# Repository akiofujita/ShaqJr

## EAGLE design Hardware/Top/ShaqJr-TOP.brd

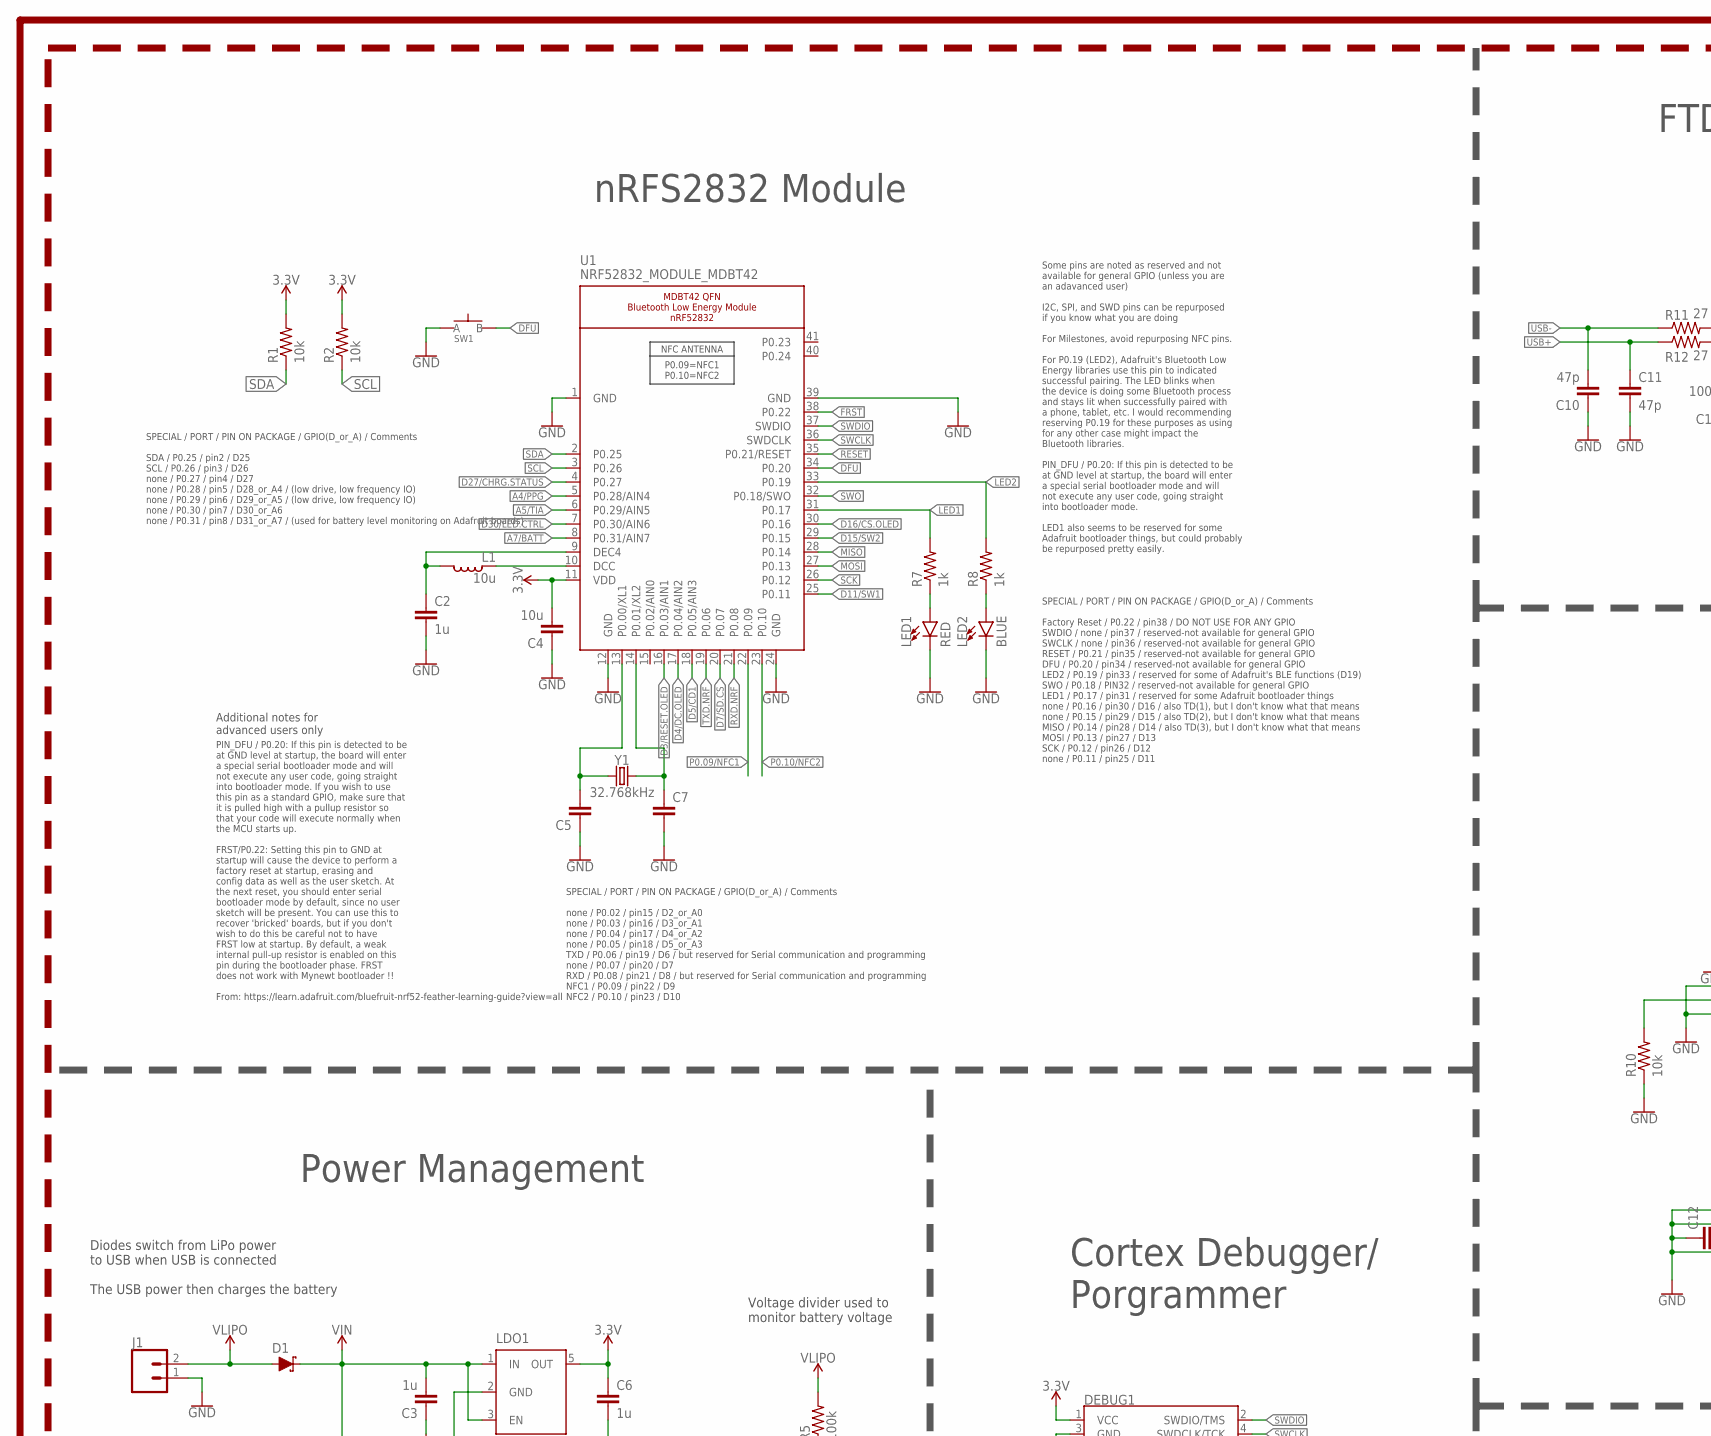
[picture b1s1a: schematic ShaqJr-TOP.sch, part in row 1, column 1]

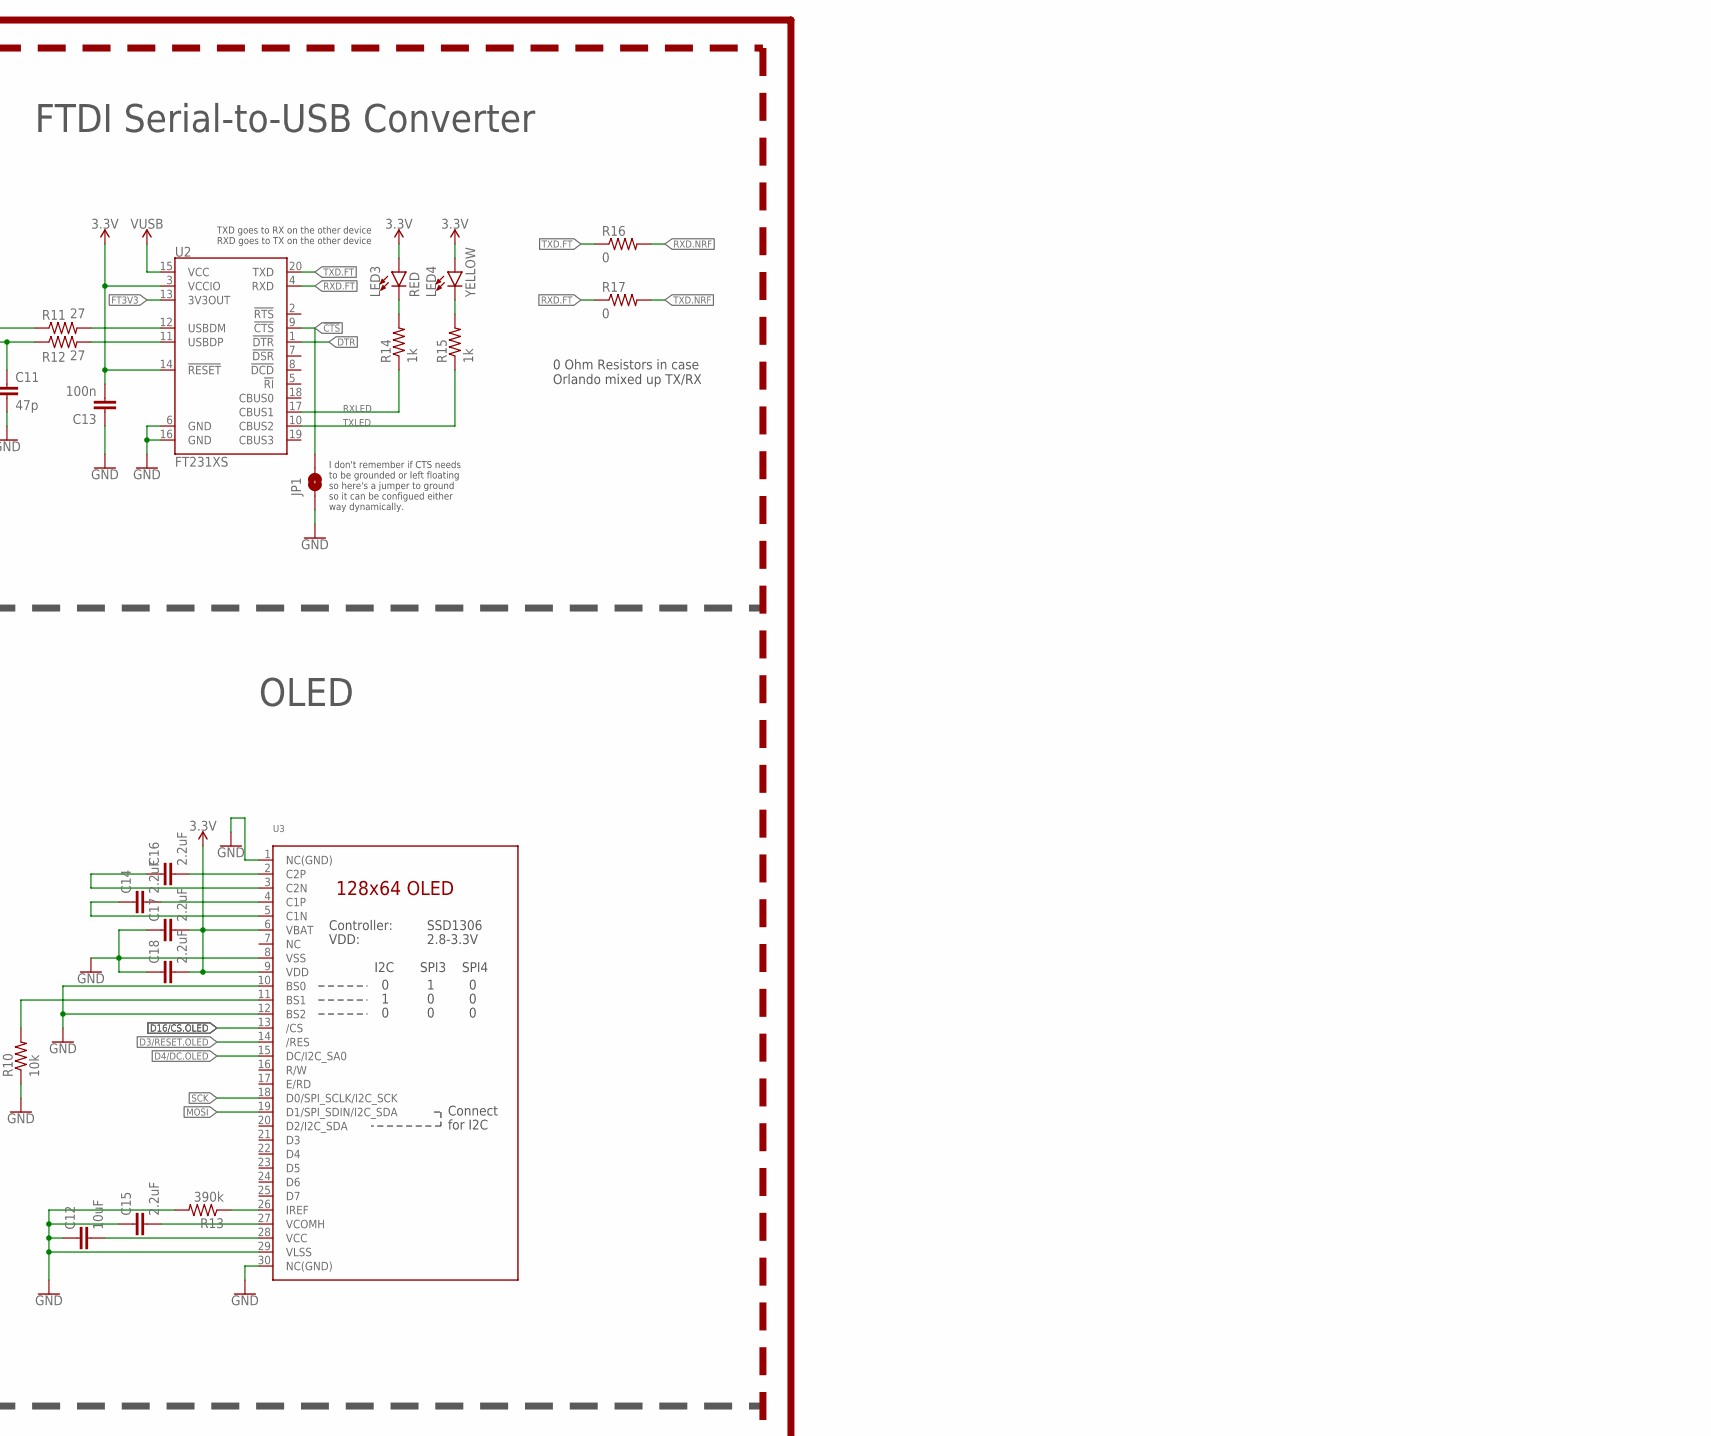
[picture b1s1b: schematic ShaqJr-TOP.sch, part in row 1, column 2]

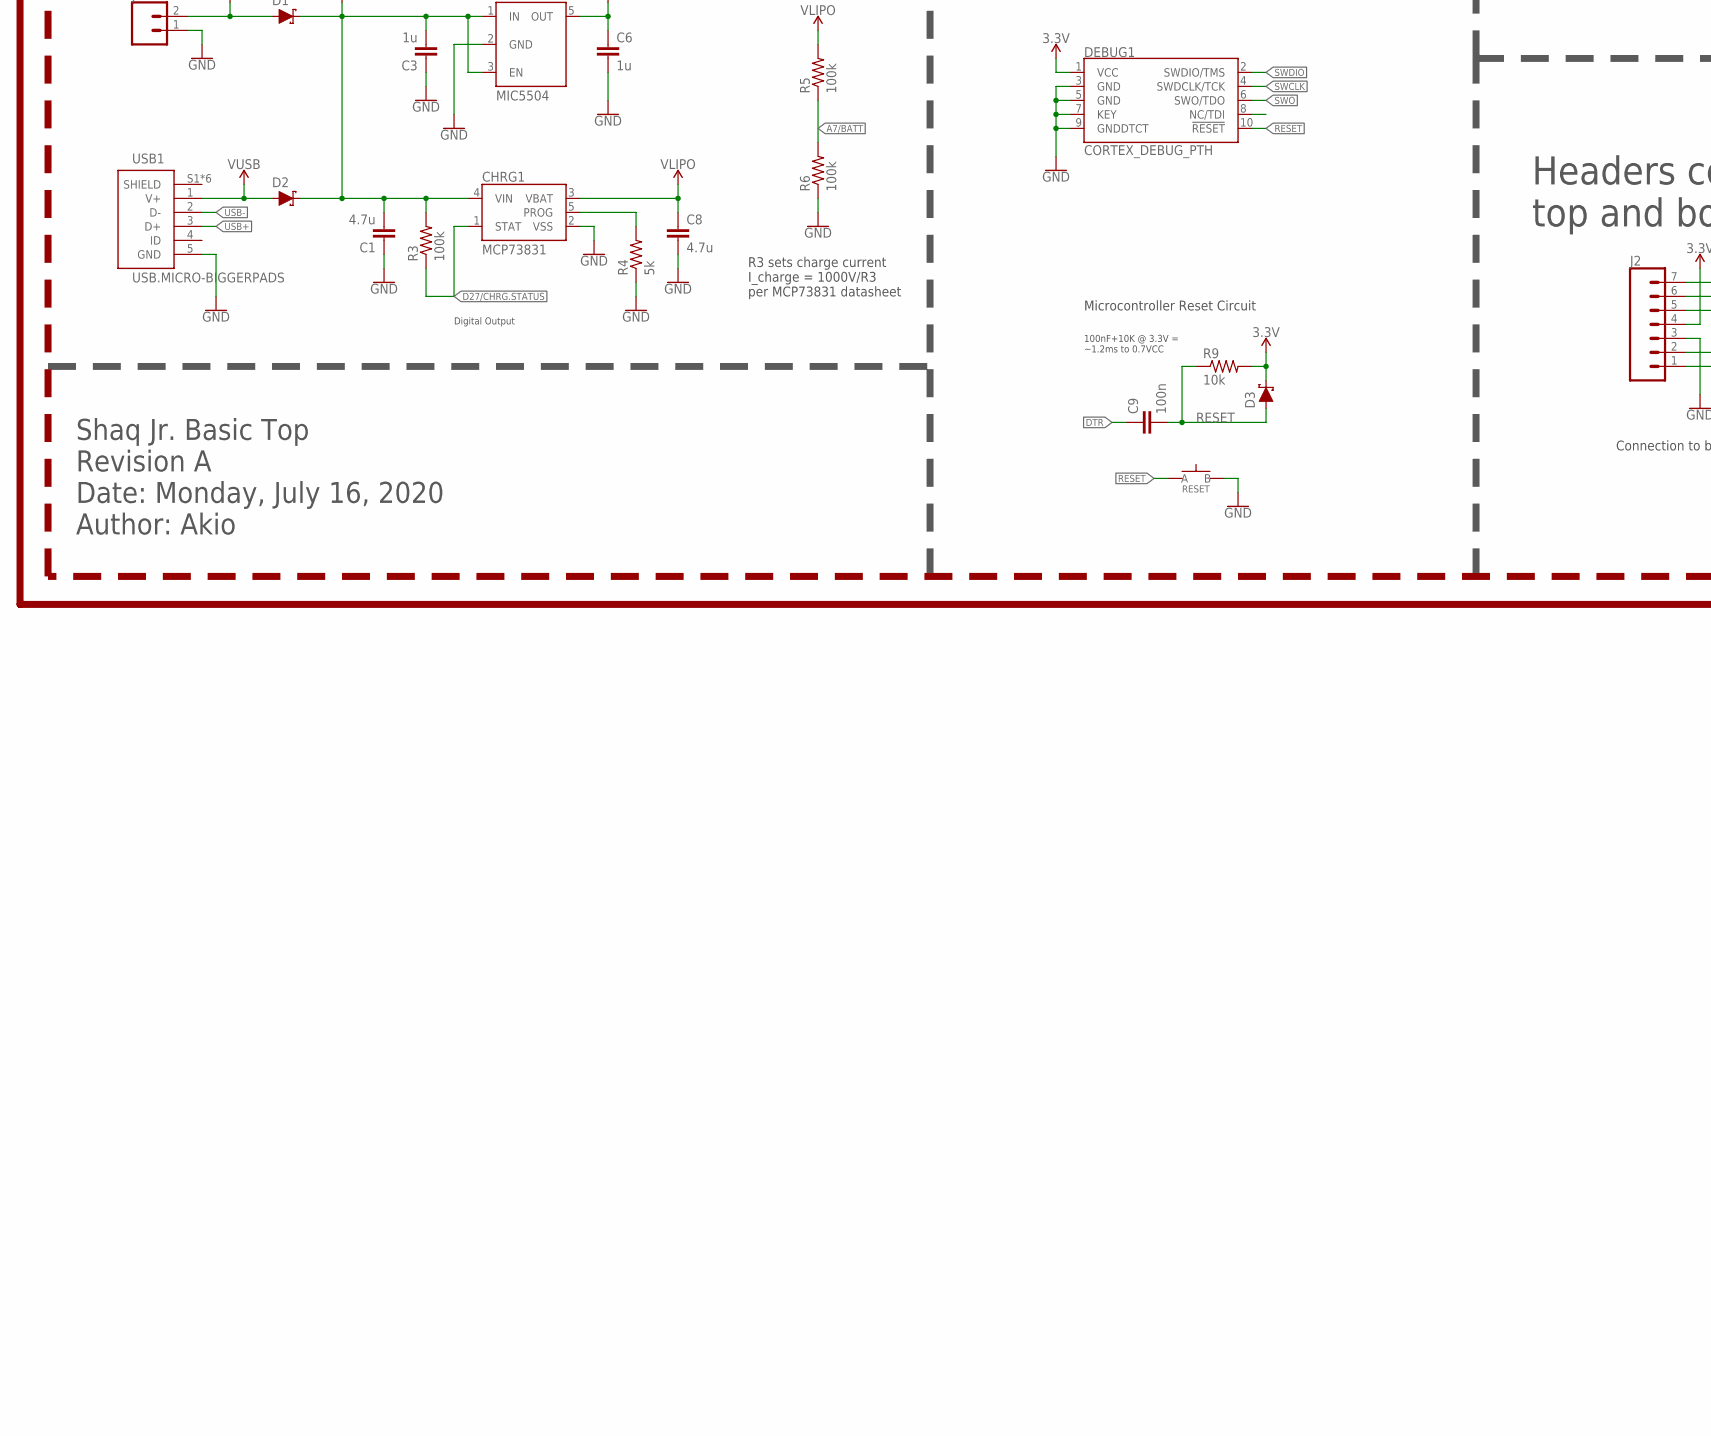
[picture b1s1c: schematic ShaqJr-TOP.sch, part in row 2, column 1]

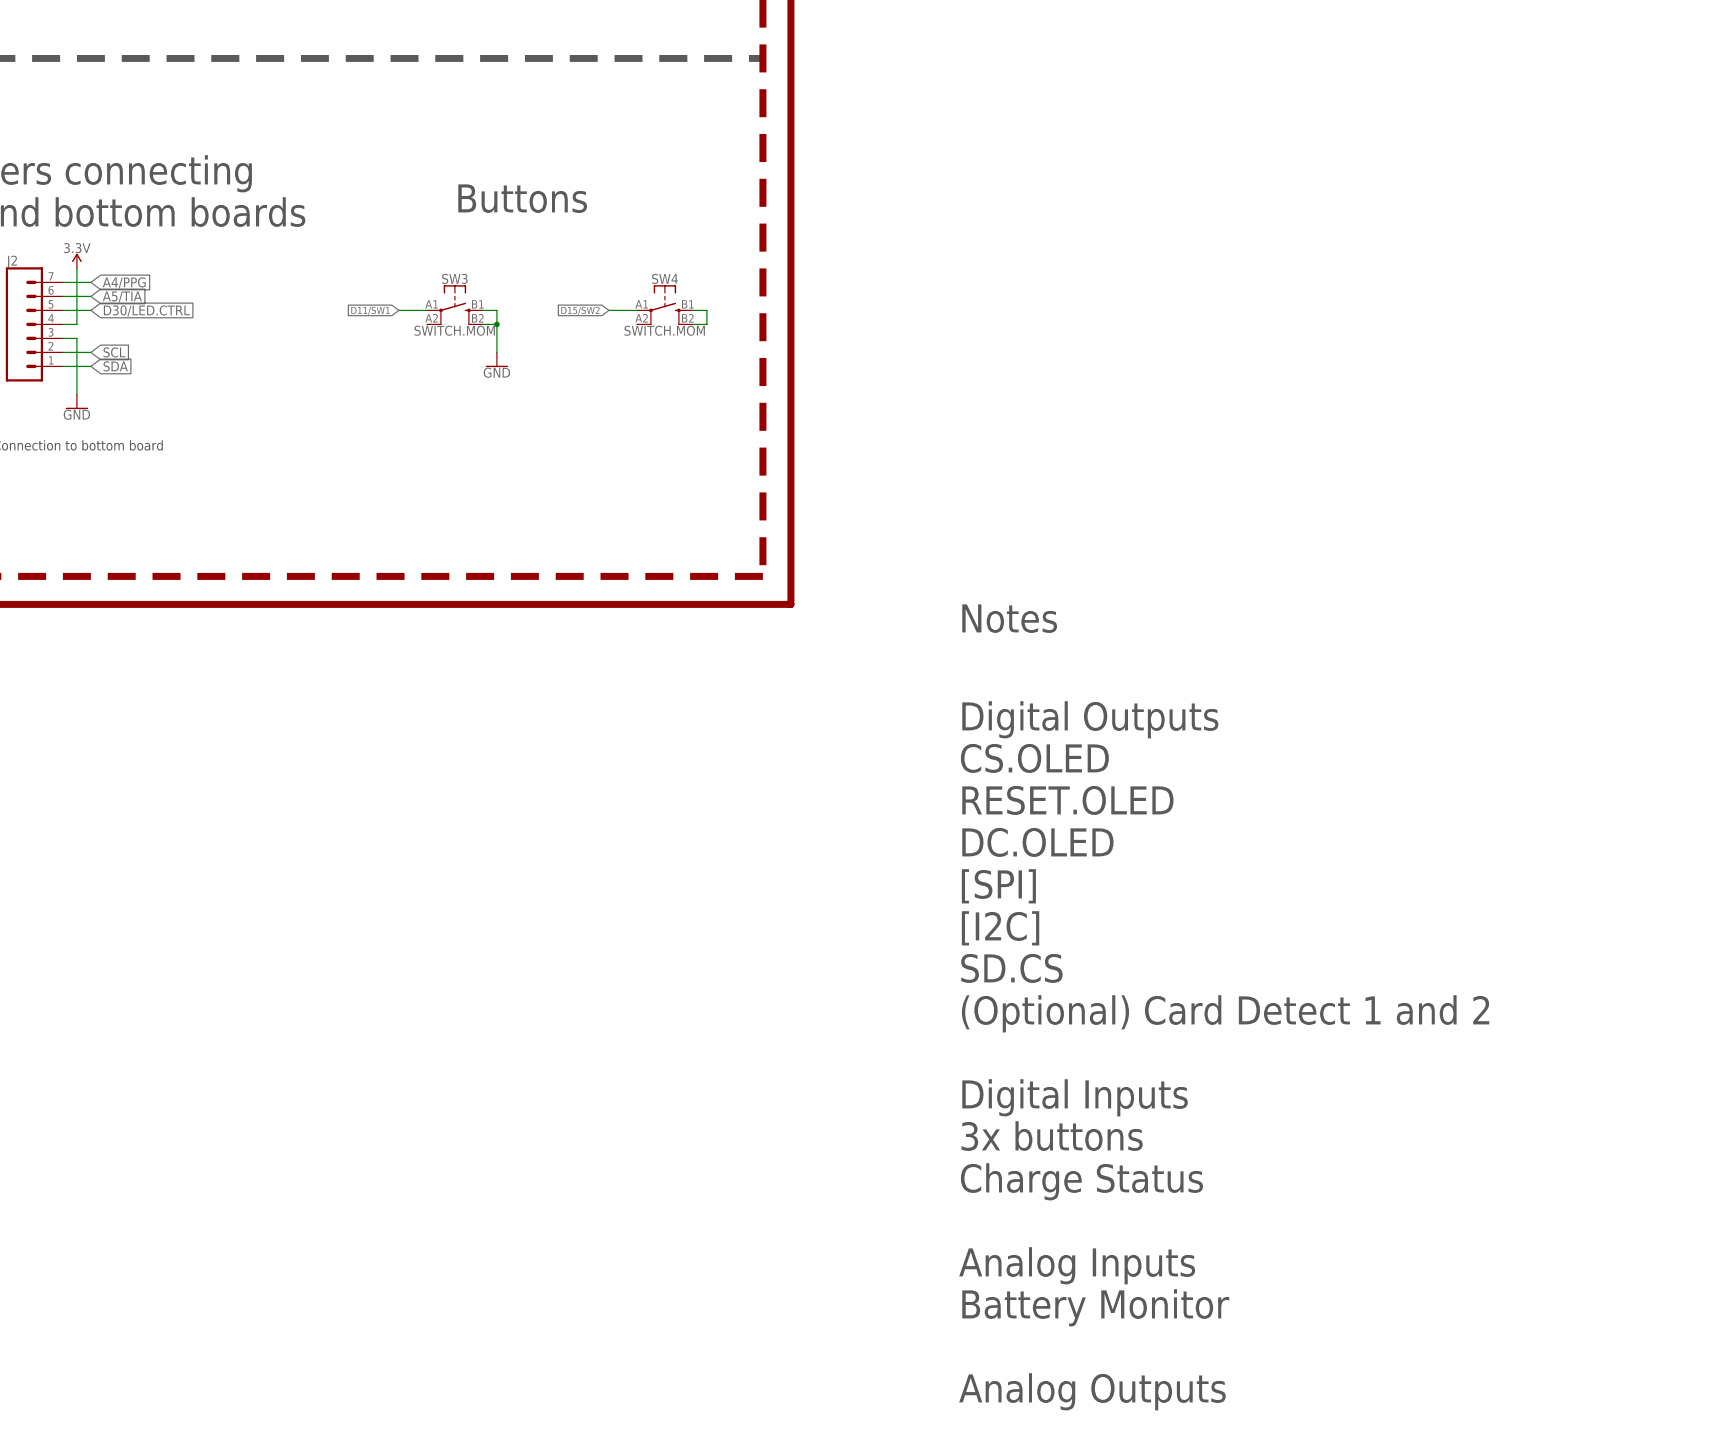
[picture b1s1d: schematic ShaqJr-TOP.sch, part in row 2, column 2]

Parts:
C1, C8: 4.7u; C0603
C2, C3, C6: 1u; C0603
C4: 10u; C0805
C5, C7: CAPACITOR0603; C0603
C9, C13: 100n; C0603
C10, C11: 47p; C0603
C12: 10uF; C0603
C14, C16, C17, C18: 2.2uF; C0402
C15: 2.2uF; C0603
CHRG1: MCP73831; SOT23-5
D1, D2, D3: SCHOTTKY-USC; USC
DEBUG1: CORTEX_DEBUG_PTH; 2X5-PTH-1.27MM
J1: CONN_02; 1X02
J2: CONN_07-1.27MM; 1X07_1.27MM
JP1: JUMPER-SMT_2_NO_SILK; SMT-JUMPER_2_NO_SILK
L1: 10u; L0603
LDO1: MIC5504; SOT23-5
LED1, LED3: RED; LED-0603
LED2: BLUE; LED-0603
LED4: YELLOW; LED-0603
R1, R2, R9, R10: 10k; R0603
R3, R5, R6: 100k; R0603
R4: 5k; R0603
R7, R8, R14, R15: 1k; R0603
R11, R12: 27; R0603
R13: 390k; R0603
R16, R17: 0; R0603
RESET: SPST-PTS830GG140-COPY.1-3; BUTTON-GULLWING
SW1: SPST-PTS830GG140-COPY.1-3; BUTTON-GULLWING
SW3, SW4: SWITCH.MOM; TACTILE_SWITCH_SMD_6.2MM_TALL
U1: NRF52832_MODULE_MDBT42; BLE_MODULE_RAYTAC_MDBT42
U2: FT231XS; SSOP20_L
U3: DISP_OLED_UG-2864HSWEG01-NO-WRAPAROUND; UG-2864HSWEG01_0.96IN_NO-WRAPAROUND
USB1: USB.MICRO-BIGGERPADS; USB-MICRO-01.BIGGERPADS
Y1: 32.768kHz; 2-SMD.NOLEAD.2.0MMTO1.2MM

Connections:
3.3V: C4.2, C6.1, C13.2, C17.2, C18.2, D3.- (C), DEBUG1.1 (VCC), J2.4, LDO1.5 (OUT), LED3.A, LED4.A, R1.2, R2.2, R9.2, U1.11 (VDD), U2.3 (VCCIO), U2.14 (!RESET), U3.6 (VBAT), U3.9 (VDD)
!CTS: JP1.2, U2.9 (!CTS)
A4/PPG: J2.7, U1.5 (P0.28/AIN4)
A5/TIA: J2.6, U1.6 (P0.29/AIN5)
A7/BATT: R5.1, R6.2, U1.8 (P0.31/AIN7)
D3/RESET.OLED: U1.16 (P0.03/AIN1), U3.14 (/RES)
D4/DC.OLED: U1.17 (P0.04/AIN2), U3.15 (DC/I2C_SA0)
D5/CD1: U1.18 (P0.05/AIN3)
D7/SD.CS: U1.20 (P0.07)
D11/SW1: SW3.A1 (1), U1.25 (P0.11)
D15/SW2: SW4.A1 (1), U1.29 (P0.15)
D16/CS.OLED: U1.30 (P0.16), U3.13 (/CS)
D27/CHRG.STATUS: CHRG1.1 (STAT), R3.1, U1.4 (P0.27)
D30/LED.CTRL: J2.5, U1.7 (P0.30/AIN6)
DFU: SW1.3 (B), U1.34 (P0.20)
DTR: C9.1, U2.1 (!DTR)
FRST: U1.38 (P0.22)
FT3V3: U2.13 (3V3OUT)
GND: C1.1, C2.2, C3.1, C4.1, C5.1, C6.2, C7.2, C8.2, C10.1, C11.2, C12.1, C13.1, C15.1, C17.1, C18.1, CHRG1.2 (VSS), DEBUG1.3 (GND), DEBUG1.5 (GND), DEBUG1.7 (KEY), DEBUG1.9 (GNDDTCT), J1.1, J2.3, JP1.1, LDO1.2 (GND), LED1.C, LED2.C, R4.1, R6.1, R10.1, R13.2, RESET.3 (B), SW1.1 (A), U1.1 (GND), U1.12 (GND), U1.24 (GND), U1.39 (GND), U2.6 (GND), U2.16 (GND), U3.1 (NC(GND)), U3.8 (VSS), U3.10 (BS0), U3.12 (BS2), U3.29 (VLSS), U3.30 (NC(GND)), USB1.5 (GND)
LED1: R7.2, U1.31 (P0.17)
LED2: R8.2, U1.33 (P0.19)
MISO: U1.28 (P0.14)
MOSI: U1.27 (P0.13), U3.19 (D1/SPI_SDIN/I2C_SDA)
unnamed: R10.2, U3.11 (BS1)
unnamed: R13.1, U3.26 (IREF)
unnamed: R11.2, U2.12 (USBDM)
unnamed: R12.2, U2.11 (USBDP)
unnamed: C16.2, U3.2 (C2P)
unnamed: C16.1, U3.3 (C2N)
unnamed: C14.2, U3.4 (C1P)
unnamed: C14.1, U3.5 (C1N)
unnamed: C12.2, U3.28 (VCC)
unnamed: C15.2, U3.27 (VCOMH)
unnamed: SW3.B1 (3), SW3.B2 (4), SW4.B1 (3), SW4.B2 (4)
unnamed: CHRG1.5 (PROG), R4.2
unnamed: LED3.C, R14.2
unnamed: LED4.C, R15.2
unnamed: C5.2, U1.13 (P0.00/XL1), Y1.P$1 (1)
unnamed: C7.1, U1.14 (P0.01/XL2), Y1.P$2 (2)
unnamed: LED1.A, R7.1
unnamed: LED2.A, R8.1
unnamed: L1.1, U1.10 (DCC)
unnamed: C2.1, L1.2, U1.9 (DEC4)
P0.09/NFC1: U1.22 (P0.09)
P0.10/NFC2: U1.23 (P0.10)
RESET: C9.2, D3.+ (A), DEBUG1.10 (!RESET), R9.1, RESET.1 (A), U1.35 (P0.21/RESET)
RXD.FT: R17.1, U2.4 (RXD)
RXD.NRF: R16.2, U1.21 (P0.08)
RXLED: R14.1, U2.17 (CBUS1)
SCK: U1.26 (P0.12), U3.18 (D0/SPI_SCLK/I2C_SCK)
SCL: J2.2, R2.1, U1.3 (P0.26)
SDA: J2.1, R1.1, U1.2 (P0.25)
SWCLK: DEBUG1.4 (SWDCLK/TCK), U1.36 (SWDCLK)
SWDIO: DEBUG1.2 (SWDIO/TMS), U1.37 (SWDIO)
SWO: DEBUG1.6 (SWO/TDO), U1.32 (P0.18/SWO)
TXD.FT: R16.1, U2.20 (TXD)
TXD.NRF: R17.2, U1.19 (P0.06)
TXLED: R15.1, U2.10 (CBUS2)
USB+: C11.1, R12.1, USB1.3 (D+)
USB-: C10.2, R11.1, USB1.2 (D-)
VIN: C1.2, C3.2, CHRG1.4 (VIN), D1.- (C), D2.- (C), LDO1.1 (IN), LDO1.3 (EN), R3.2
VLIPO: C8.1, CHRG1.3 (VBAT), D1.+ (A), J1.2, R5.2
V_USB: D2.+ (A), U2.15 (VCC), USB1.1 (V+)

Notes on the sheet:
nRFS2832 Module
OLED
Power Management
Buttons
Cortex Debugger/ Porgrammer
Digital Outputs CS.OLED RESET.OLED DC.OLED [SPI] [I2C] SD.CS (Optional) Card Detect 1 and 2 Digital Inputs 3x buttons Charge Status Analog Inputs Battery Monitor Analog Outputs
Microcontroller Reset Circuit
100nF+10K @ 3.3V = ~1.2ms to 0.7VCC
SPECIAL / PORT / PIN ON PACKAGE / GPIO(D_or_A) / Comments SDA / P0.25 / pin2 / D25 SCL / P0.26 / pin3 / D26 none / P0.27 / pin4 / D27 none / P0.28 / pin5 / D28_or_A4 / (low drive, low frequency IO) none / P0.29 / pin6 / D29_or_A5 / (low drive, low frequency IO) none / P0.30 / pin7 / D30_or_A6 none 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
SPECIAL / PORT / PIN ON PACKAGE / GPIO(D_or_A) / Comments none / P0.02 / pin15 / D2_or_A0 none / P0.03 / pin16 / D3_or_A1 none / P0.04 / pin17 / D4_or_A2 none / P0.05 / pin18 / D5_or_A3 TXD / P0.06 / pin19 / D6 / but reserved for Serial communication and programming none / P0.07 / pin20 / D7 RXD / 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
SPECIAL / PORT / PIN ON PACKAGE / GPIO(D_or_A) / Comments Factory Reset / P0.22 / pin38 / DO NOT USE FOR ANY GPIO SWDIO / none / pin37 / reserved-not available for general GPIO SWCLK / none / pin36 / reserved-not available for general GPIO RESET / P0.21 / pin35 / reserved-not available for general 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
Some pins are noted as reserved and not available for general GPIO (unless you are an adavanced user) I2C, SPI, and SWD pins can be repurposed if you know what you are doing For Milestones, avoid repurposing NFC pins. For P0.19 (LED2), Adafruit's Bluetooth Low Energy libraries use this pin to indic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
PIN_DFU / P0.20: If this pin is detected to be at GND level at startup, the board will enter a special serial bootloader mode and will not execute any user code, going straight into bootloader mode. If you wish to use this pin as a standard GPIO, make sure that it is pulled high with a pullup resis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
Additional notes for advanced users only
TXD goes to RX on the other device RXD goes to TX on the other device
I don't remember if CTS needs to be grounded or left floating so here's a jumper to ground so it can be configued either way dynamically.
FTDI Serial-to-USB Converter
Notes
Connection to bottom board
Digital Output
Shaq Jr. Basic Top Revision A Date: Monday, July 16, 2020 Author: Akio
Diodes switch from LiPo power to USB when USB is connected The USB power then charges the battery
R3 sets charge current I_charge = 1000V/R3 per MCP73831 datasheet
Voltage divider used to monitor battery voltage
Headers connecting top and bottom boards
0 Ohm Resistors in case Orlando mixed up TX/RX

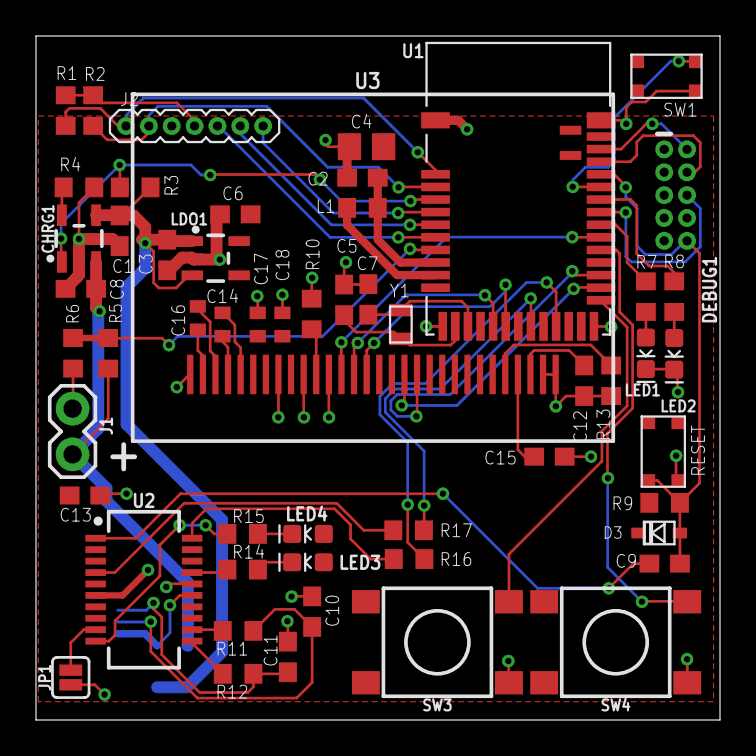
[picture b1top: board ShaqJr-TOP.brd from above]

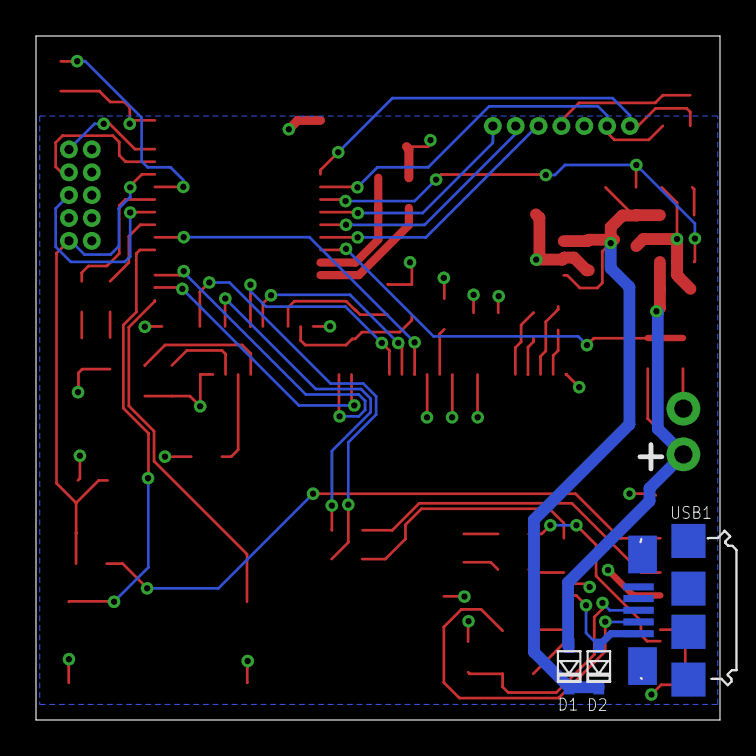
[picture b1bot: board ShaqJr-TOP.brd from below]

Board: 2 copper layers, 38.0 x 38.0 mm, 58 parts (3 on the bottom side), 56 nets.

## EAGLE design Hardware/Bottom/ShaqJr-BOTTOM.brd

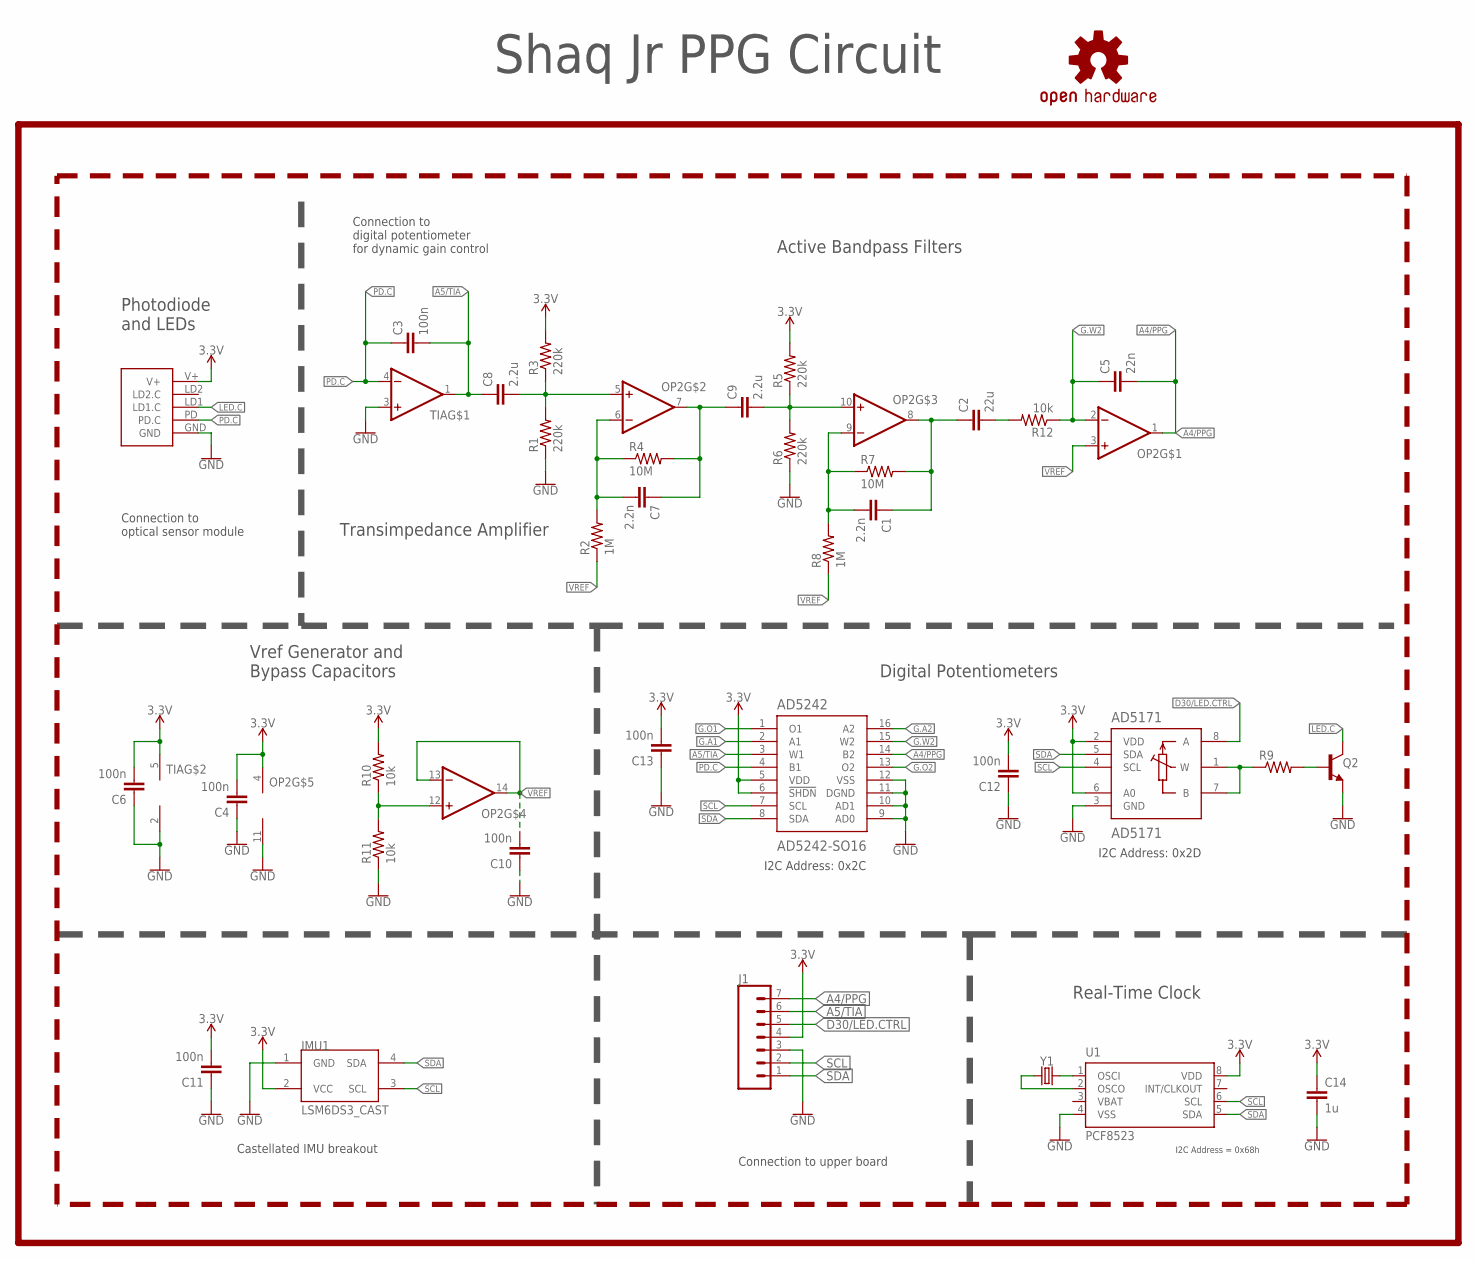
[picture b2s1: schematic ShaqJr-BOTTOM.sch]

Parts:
AD5171: AD5171; SOT-23-8
AD5242: AD5242-SO16; SO16
C1, C7: 2.2n; C0603
C2: 22u; C0603
C3, C4, C6, C10, C11, C12, C13: 100n; C0603
C5: 22n; C0603
C8, C9: 2.2u; C0603
C14: 1u; C0603
IMU1: LSM6DS3_CAST
J1: CONN_07-1.27MM; 1X07_1.27MM
LOGO1: REVISION.A; REV.A
LOGO2: OSHW-LOGOS; OSHW-LOGO-S
OP2: OP-QUAD-SO14; SO14
Q2: NPN-GENERIC; SOT23-3
R1, R3, R5, R6: 220k; R0603
R2, R8: 1M; R0603
R4, R7: 10M; R0603
R9: RESISTOR0603; R0603
R10, R11: 10k; R0402
R12: 10k; R0603
TIA: OP-SINGLEOT; SOT23-5
U1: PCF8523; SO8; DIGIKEY 568-5306-1-ND
U$1: PPG.MODULE.2
Y1: 32.7680kHz; 2-SMD.NOLEAD.2.0MMTO1.2MM

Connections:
3.3V: AD5171.2 (VDD), AD5171.6 (A0), AD5242.5 (VDD), AD5242.6 (!SHDN), C4.2, C6.2, C11.2, C12.2, C13.2, C14.1, IMU1.2 (VCC), J1.4, OP2.4 (V+), R3.2, R5.2, R10.2, TIA.5 (V+), U1.8 (VDD), U$1.V+
A4/PPG: AD5242.14 (B2), C5.2, J1.7, OP2.1 (OUT)
A5/TIA: AD5242.3 (W1), C3.2, C8.1, J1.6, TIA.1 (OUT)
D30/LED.CTRL: AD5171.8 (A), J1.5
G.A1: AD5242.2 (A1)
G.A2: AD5242.16 (A2)
G.O1: AD5242.1 (O1)
G.O2: AD5242.13 (O2)
G.W2: AD5242.15 (W2), C5.1, OP2.2 (-IN), R12.1
GND: AD5171.3 (GND), AD5242.9 (AD0), AD5242.10 (AD1), AD5242.11 (DGND), AD5242.12 (VSS), C4.1, C6.1, C10.1, C11.1, C12.1, C13.1, C14.2, IMU1.1 (GND), J1.3, OP2.11 (V-), Q2.2 (E), R1.1, R6.1, R11.1, TIA.2 (V-), TIA.3 (+IN), U1.4 (VSS), U$1.GND
LED.C: Q2.3 (C), U$1.LD1 (LD1.C)
unnamed: C8.2, OP2.5 (+IN), R1.2, R3.1
unnamed: C9.2, OP2.10 (+IN), R5.1, R6.2
unnamed: C7.2, OP2.6 (-IN), R2.2, R4.1
unnamed: C7.1, C9.1, OP2.7 (OUT), R4.2
unnamed: C1.2, OP2.9 (-IN), R7.1, R8.2
unnamed: C1.1, C2.1, OP2.8 (OUT), R7.2
unnamed: C2.2, R12.2
unnamed: U1.2 (OSCO), Y1.P$1 (1)
unnamed: U1.1 (OSCI), Y1.P$2 (2)
unnamed: Q2.1 (B), R9.2
unnamed: AD5171.1 (W), AD5171.7 (B), R9.1
unnamed: OP2.12 (+IN), R10.1, R11.2
PD.C: AD5242.4 (B1), C3.1, TIA.4 (-IN), U$1.PD (PD.C)
SCL: AD5171.4 (SCL), AD5242.7 (SCL), IMU1.3 (SCL), J1.2, U1.6 (SCL)
SDA: AD5171.5 (SDA), AD5242.8 (SDA), IMU1.4 (SDA), J1.1, U1.5 (SDA)
VBAT: U1.3 (VBAT)
VREF: C10.2, OP2.3 (+IN), OP2.13 (-IN), OP2.14 (OUT), R2.1, R8.1

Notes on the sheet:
Photodiode and LEDs
Active Bandpass Filters
Digital Potentiometers
Transimpedance Amplifier
I2C Address: 0x2C
I2C Address: 0x2D
Connection to optical sensor module
Connection to digital potentiometer for dynamic gain control
Connection to upper board
Castellated IMU breakout
Vref Generator and Bypass Capacitors
Shaq Jr PPG Circuit
Real-Time Clock
I2C Address = 0x68h

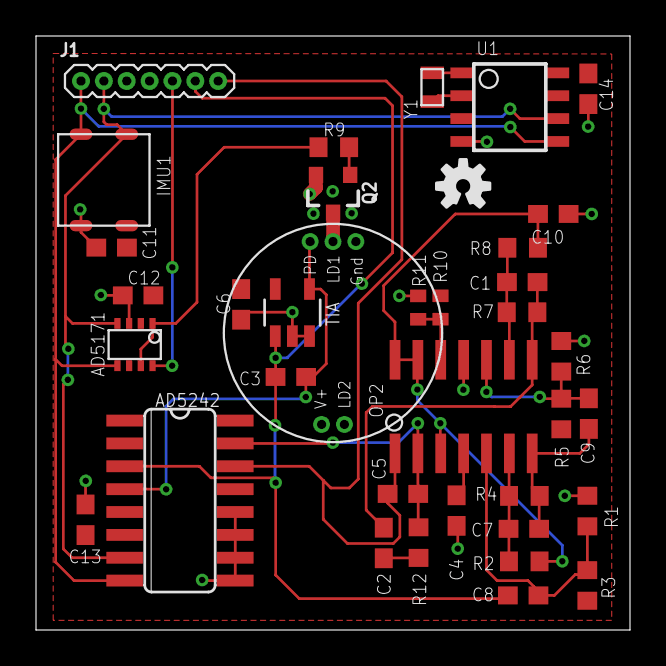
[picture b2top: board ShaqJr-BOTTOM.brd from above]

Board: 2 copper layers, 33.0 x 33.0 mm, 38 parts (0 on the bottom side), 23 nets.

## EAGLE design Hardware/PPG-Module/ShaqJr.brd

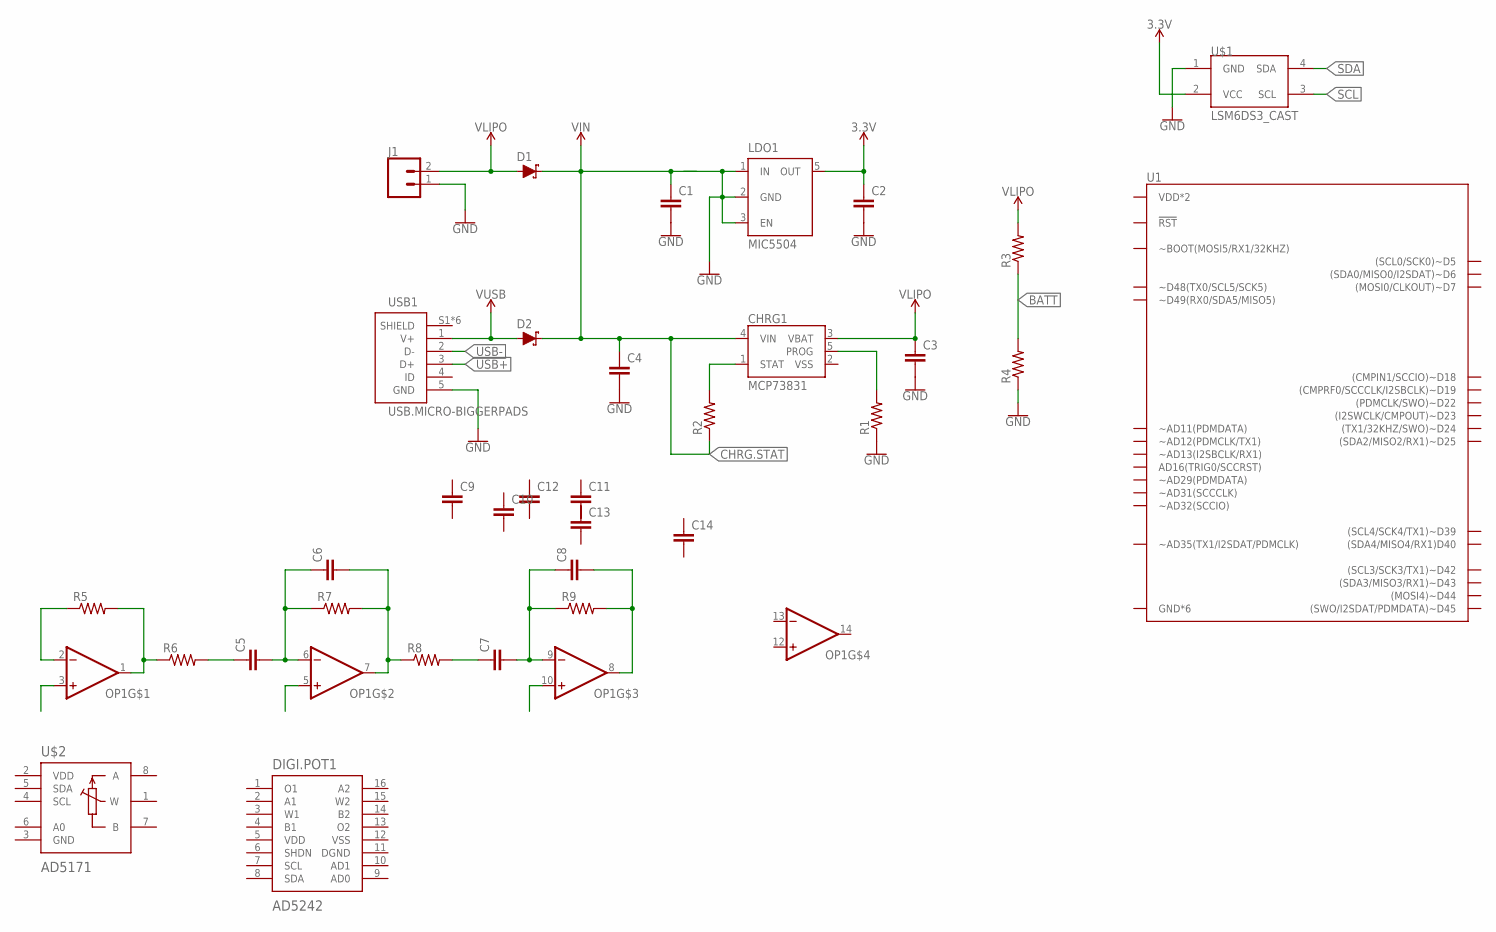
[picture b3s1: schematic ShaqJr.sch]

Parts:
C1, C2, C3, C4, C5, C6, C7, C8, C9, C10, C11, C12, C13, C14: CAPACITOR0603; C0603
CHRG1: MCP73831; SOT23-5
D1, D2: SCHOTTKY-USC; USC
DIGI.POT1: AD5242; TSSOP16
J1: CONN_02; 1X02
LDO1: MIC5504; SOT23-5
OP1: OP-QUAD-SO14; SO14
R1, R2, R3, R4, R5, R6, R7, R8, R9: RESISTOR0603; R0603
U1: ARTEMIS.CAST; ARTEMIS_CAST
U$1: LSM6DS3_CAST
U$2: AD5171; SOT-23-8
USB1: USB.MICRO-BIGGERPADS; USB-MICRO-01.BIGGERPADS

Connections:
3.3V: C2.1, LDO1.5 (OUT)
BATT: R3.1, R4.2
CHRG.STAT: C1.1, C4.1, CHRG1.4 (VIN), D1.- (C), D2.- (C), R2.1
GND: C1.2, C2.2, C3.2, C4.2, J1.1, LDO1.1 (IN), LDO1.2 (GND), LDO1.3 (EN), R1.1, R4.1, USB1.5 (GND)
unnamed: OP1.2 (-IN), R5.1
unnamed: OP1.1 (OUT), R5.2, R6.1
unnamed: CHRG1.5 (PROG), R1.2
unnamed: CHRG1.1 (STAT), R2.2
unnamed: C5.1, R6.2
unnamed: C5.2, C6.1, OP1.6 (-IN), R7.1
unnamed: C7.1, R8.2
unnamed: C6.2, OP1.7 (OUT), R7.2, R8.1
unnamed: C7.2, C8.1, OP1.9 (-IN), R9.1
unnamed: C8.2, OP1.8 (OUT), R9.2
SCL: U$1.3 (SCL)
SDA: U$1.4 (SDA)
USB+: USB1.3 (D+)
USB-: USB1.2 (D-)
V+: OP1.4 (V+)
V-: OP1.11 (V-)
VLIPO: C3.1, CHRG1.3 (VBAT), D1.+ (A), J1.2, R3.2
VSS: CHRG1.2 (VSS)
V_USB: D2.+ (A), USB1.1 (V+)

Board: 2 copper layers, 34 parts (0 on the bottom side), 16 nets, no tracks yet.
